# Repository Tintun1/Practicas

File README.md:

# Practicas de programacion / diseño / demas

en este repositorio voy a documentar los ejercicios mayormente realizados a lo largo de mi aprendizaje de las diferentes areas aplicadas, estos ejercicios pueden ser ayuda para los que desean ejercitar sus conocimientos sobre las areas existentes en este repositorio.

## En caso de encontrar errores

En el caso de encontrar errores o diferentes formas de llegar a un objetivo en comun, va a ser bienvenida la subida de un commit o correccion de la trayectoria

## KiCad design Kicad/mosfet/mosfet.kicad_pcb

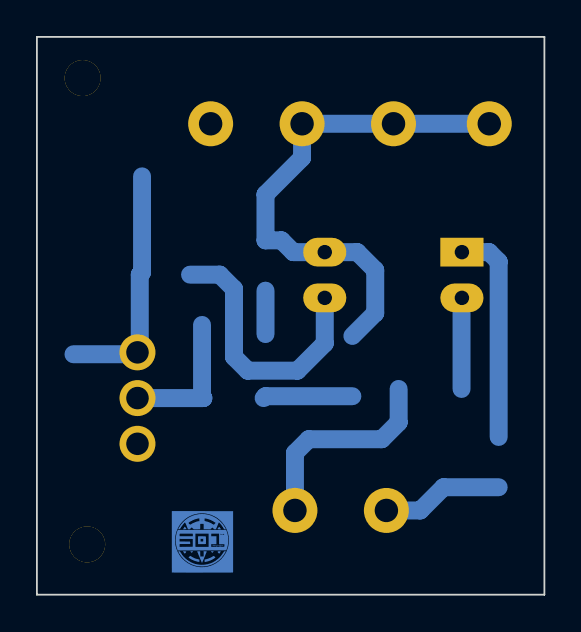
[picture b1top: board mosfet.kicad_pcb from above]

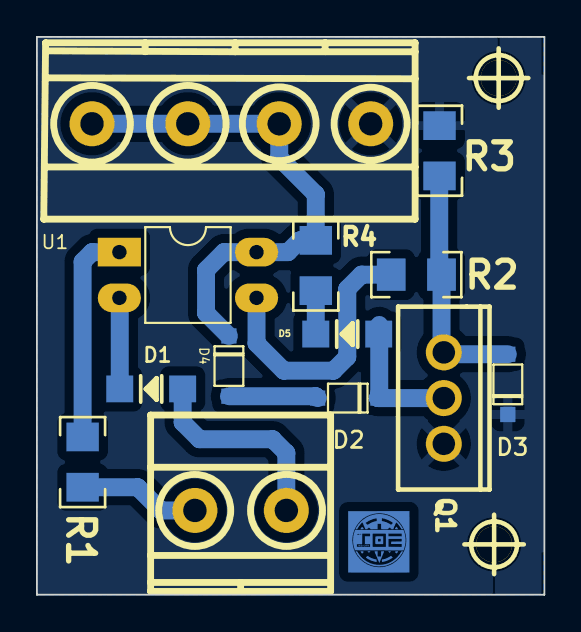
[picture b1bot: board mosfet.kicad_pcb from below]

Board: 2 copper layers, 28.2 x 31.0 mm, 15 parts (15 on the bottom side), 11 nets.

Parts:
D1, D5: LED; LED_1206
D2: 1N4148; sod123
D3: 1N5819WS; sod123
D4: 1N4752; sod123
H1, H2: MountingHole_Pad; hole_2mm
J1: TB_1X2; BORNERA2
J3: TB_1X4; TB_X4
Q1: IRFZ44N; TO-220
R1: 220; R_1206
R2, R3: 10k; R_1206
R4: 5,6k; R_1206
U1: PC817; DIP-4_PC817

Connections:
/OUT-: D2.2 (A), D5.1 (K), Q1.2 (D)
GND: D3.2 (A), J3.1, Q1.3 (S), R3.1
unnamed: D1.2 (A), U1.2
unnamed: D1.1 (K), J1.2
unnamed: D2.1 (K), D4.1 (K)
unnamed: D3.1 (K), Q1.1 (G), R2.2, R3.2
unnamed: D5.2 (A), R4.1
unnamed: J1.1, R1.1
unnamed: R1.2, U1.1
unnamed: R2.1, U1.3
VCC: D4.2 (A), J3.2, J3.3, R4.2, U1.4

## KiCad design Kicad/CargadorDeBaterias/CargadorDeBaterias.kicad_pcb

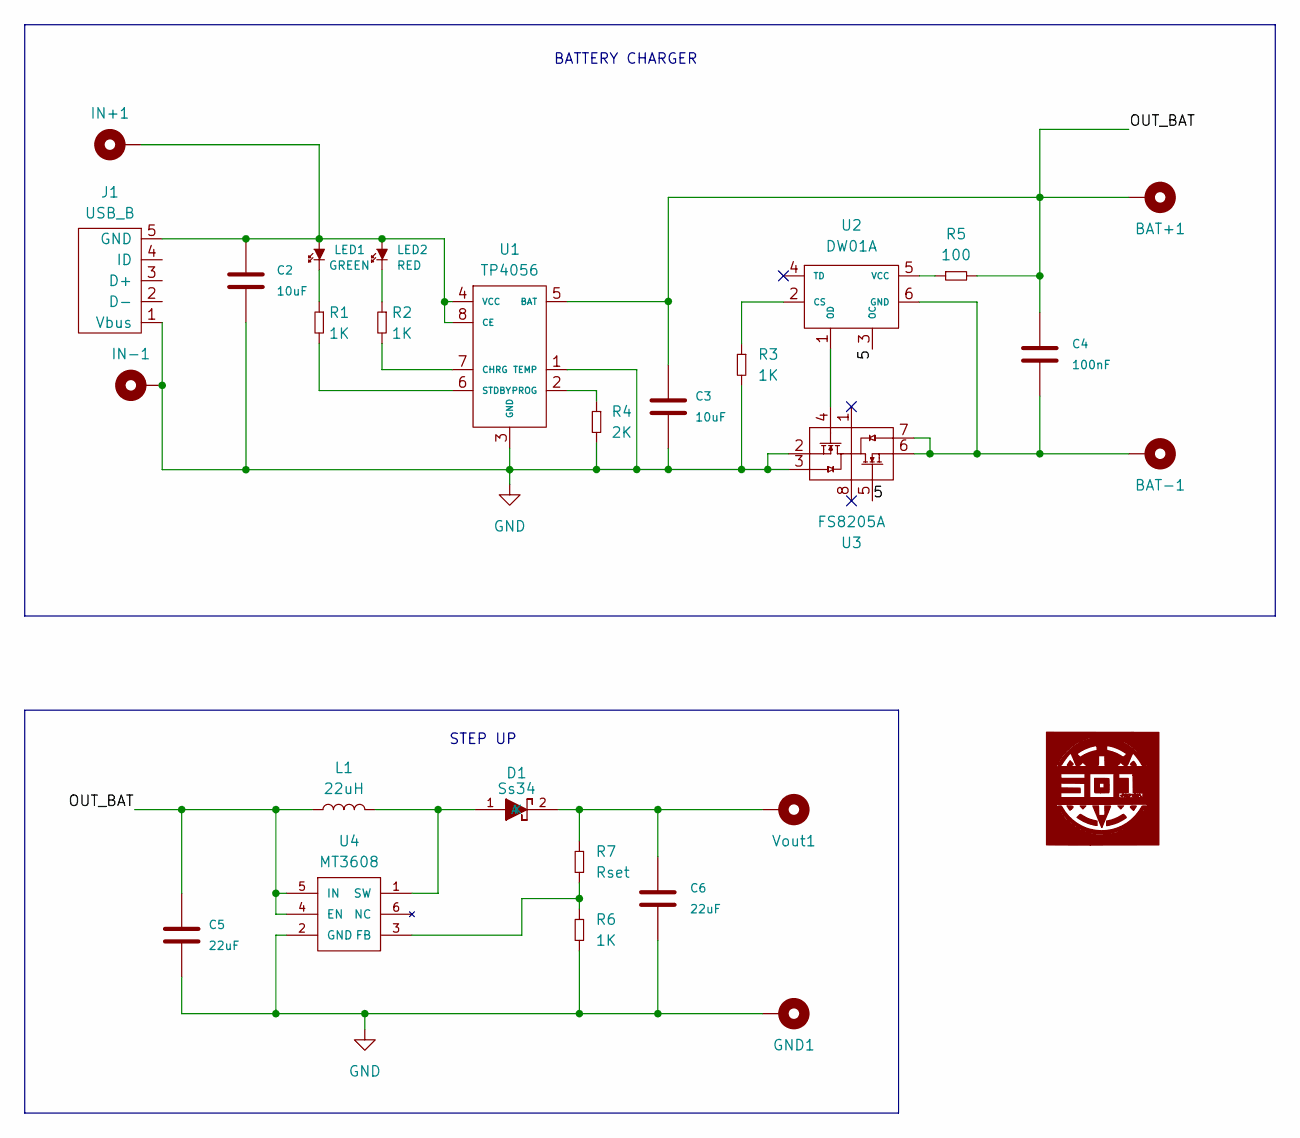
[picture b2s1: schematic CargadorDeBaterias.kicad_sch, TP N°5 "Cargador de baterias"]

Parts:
BAT+1: MountingHole_Pad; Clable
BAT-1: MountingHole_Pad; Clable
C2: 10uF; C_0805
C3: 10uF; C_0603
C4: 100nF; C_0603
C5, C6: 22uF; C_1206
D1: Ss34; DO-214AB
GND1: MountingHole_Pad; Clable
IN+1: MountingHole_Pad; Clable
IN-1: MountingHole_Pad; Clable
J1: USB_B; USB_Micro-B
L1: 22uH; CDRH104R
LED1: GREEN; Led_0805
LED2: RED; Led_0805
R1, R2, R3, R6: 1K; R_0603
R4: 2K; R_0603
R5: 100; R_0603
R7: Rset; R_0603
U1: TP4056; ESOP-8
U2: DW01A; SOT-23-6
U3: FS8205A; TSSOP-8
U4: MT3608; SOT-23-6
Vout1: MountingHole_Pad; Clable

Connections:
/5: U2.3 (OC), U3.5
/OUT_BAT: BAT+1.1, C3.1, C4.1, C5.1, L1.1, R5.2, U1.5 (BAT), U4.4 (EN), U4.5 (IN)
GND: C2.2, C3.2, C5.2, C6.2, GND1.1, IN-1.1, J1.1 (Vbus), R3.2, R4.2, R6.2, U1.1 (TEMP), U1.3 (GND), U3.2, U3.3, U4.2 (GND)
unnamed: D1.1 (A), L1.2, U4.1 (SW)
unnamed: C6.1, D1.2 (K), R7.1, Vout1.1
unnamed 5: C2.1, IN+1.1, J1.5 (GND), LED1.1 (A), LED2.1 (A), U1.4 (VCC), U1.8 (CE); also elsewhere on the board
unnamed 6: LED1.2 (K), R1.1; also elsewhere on the board
unnamed: LED2.2 (K), R2.1
unnamed: R2.2, U1.7 (CHRG)
unnamed: R4.1, U1.2 (PROG)
unnamed: R1.2, U1.6 (STDBY)
unnamed: R3.1, U2.2 (CS)
unnamed: BAT-1.1, C4.2, U2.6 (GND), U3.6, U3.7
unnamed: U2.1 (OD), U3.4
unnamed: R5.1, U2.5 (VCC)
unnamed: R6.1, R7.2, U4.3 (FB)

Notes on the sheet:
STEP UP
BATTERY CHARGER

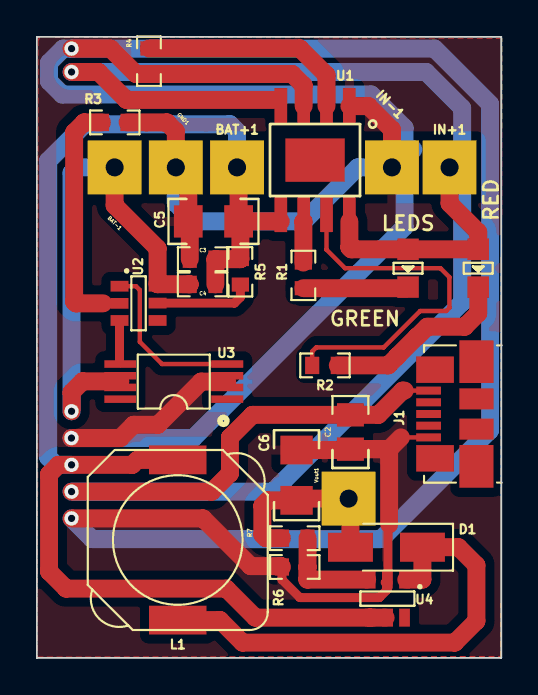
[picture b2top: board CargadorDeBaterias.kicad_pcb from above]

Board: 2 copper layers, 25.8 x 34.5 mm, 27 parts (0 on the bottom side), 16 nets.

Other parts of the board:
LEDS: GREEN; Led_0805

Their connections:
unnamed 5: LEDS.1 (A); also elsewhere on the board
unnamed 6: LEDS.2 (K); also elsewhere on the board

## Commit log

2024-03-23 Creacion del repositorio
    Creacion del repositorio
2024-03-23 fix
    fix
